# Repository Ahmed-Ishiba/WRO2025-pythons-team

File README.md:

<p align="center">

</p>  

Documentation of our self-driving car for the **WRO 2025 Future Engineers** category.

Our team members:
- **Ahmed Ibrahim Elsayed** — Software lead  
- **Eyad Ahmed Nazary** — Electrical lead  
- **Nour Eldin Raoof** — Mechanical design & fabrication  
- **Omar Khaled** — Coach and mentor  

---

## Content

1. [Project Overview](#project-overview)  
    1. [What is WRO?](#what-is-wro)  
    2. [Team Introduction](#team-introduction)  
    3. [Our Mission](#our-mission)  
2. [System Design](#system-design)  
    1. [Robot Architecture](#robot-architecture)  
    2. [Design Philosophy](#design-philosophy)  
    3. [System Diagram](#system-diagram)  
    4. [Bill of Materials](#bill-of-materials)  
3. [Hardware](#hardware)  
    1. [Mechanical](#mechanical)  
    2. [Electrical](#electrical)  
4. [Software](#software)  
    1. [Brief Overview](#brief-overview)  
    2. [Code flow chart](#flow-chart)  
5. [MATLAB Modeling & Simulation](#modelling-and-simulation)  
    1. [Model Overview](#model-overview)  
    2. [Problem Context and Strategy](#problem-context-and-strategy)  
    3. [Modeling and Simulation](#modelling-and-simulation)
        1. [Simulink Logical Model](#simulink-logical-model)
        2. [Complementary Filter Subsystem](#complementary-filter-sub-system)
        3. [Stateflow Diagram](#state-flow-diagram)
        4. [MATLAB Function](#matlab-function)
        5. [Simscape Electrical Model](#simscape-electrical-model)  
    4. [Testing and Verification](#testing-and-verification)  
6. [Testing & Calibration](#testing-and-calibration)
7. [Reproduce Our Robot: Step-by-Step Guide](#reproduce-our-robot)
8. [Future Improvements](#future-improvements)
9. [Team photo](#team-photo)  

## Project Overview

### What is WRO?

WRO (World Robot Olympiad), specifically the **Future Engineers** category, is a competition created to foster passion for STEM. The Future Engineers category is designed for university students. The challenge changes every 3 years, and this year the theme is **autonomous driving**.  
The robot must be designed to drive around a track **completely autonomously**, without external human intervention.

### Team Introduction

We are the **third generation** of *The Pythons* team.  
Our team consists of 3 members and a coach:

1. **Ahmed Ibrahim Elsayed (me):** Software lead — 2nd year, Faculty of Engineering, Alexandria University  
2. **Eyad Ahmed Nazary:** Electrical lead — 1st year, AASTMT  
3. **Nour Eldin Raoof:** Mechanical lead — 3rd year, Faculty of Science, Alexandria University  
4. **Omar Khaled:** Team coach — AASTMT

We have been participating in robotics competitions since **2016**, and we joined The Pythons team in **2017**.

### Our Mission

Our main mission in robotics competitions is to **improve ourselves**, gain experience, and meet like-minded people.  
We specifically enjoy WRO because it **encourages open-source work**, allowing teams to learn from each other, share solutions, and build stronger communities.
.
## System Design:
  ### Robot architecture:   
The main input sources are the camera, ultrasonic sensors to measure distance from walls, Time Of Flight sensors to measure distance from obstacles and parking lot walls, MPU6050 sensor to measure orientation angle for corner rotation and to ensure parallel parking.  
Then the raspberry pi processes these input data and outputs character to KB2040 to control servo and DC motors

  ### Design philosophy:
  When designing our robot we always made sure that our design follows a modular design that is easy to comprehend and troubleshoot, which helps us in improving it with ease, this approach also minimizes time delays that may happen due to fabrication and unfortunate mishaps, this also helps anyone without experience in robotics and future teams to pick up where we left off.
  ### System diagram:  

This diagram shows the main components of the robot and how they communicate.  
- The Raspberry Pi 5 acts as the central controller, running the main software and decision-making algorithms.  
- It communicates with ESP32 microcontroller and KB2040 via UART.  
- The KB2040 handles all real-time tasks such as controlling the servo and DC motors through PWM signals.  
-  All controllers share a common power source with independent voltage regulation for stability.

<br>  

  ### Bill Of Materials:   
  
| Component Name | Number of Items | Price (EGP) | Price (USD) |
|----------------|-----------------|--------------|--------------|
| Google Coral Accelerator | x1 | 6,250.00 | 125.00 |
| ESP32 Supermini | x1 | 350.00 | 7.00 |
| KB2040 | x1 | 425.00 | 8.50 |
| Raspberry Pi 5 | x1 | 4,000.00 | 80.00 |
| IMU MPU6050 | x1 | 125.00 | 2.50 |
| Step Down Converter 12V→5V | x1 | 450.00 | 9.00 |
| Wheels | x4 | 473.00 | 9.45 |
| Motor | x1 | 350.00 | 7.00 |
| Servo (180°) | x1 | 150.00 | 3.00 |
| Arducam | x1 | 3,000.00 | 60.00 |
| Step Down Converter 12V→3.3V | x2 | 35.00 | 0.70 |
| 12V Battery | x1 | 450.00 | 9.00 |
| Ultrasonic Sensor | x2 | 45.00 | 0.90 |
| Motor Driver IC | x1 | 100.00 | 2.00 |
| Big Ball Bearings | x2 | 100.00 | 2.00 |
| Small Ball Bearings | x2 | 50.00 | 1.00 |
| PCB Fabrication | x1 | 1,250.00 | 25.00 |
|Time Of Flight sensor | x2 | _ | _ |
| **Total** | — | **17,186.50** | **363.41** |
## Hardware:
This section includes brief overview of hardware section of robot (Mechanical and electrical).  
Each section is explained in detail in it's respective folder  
SLDPRT, DXF and board files are also included in their respective folder to download, print and get down to business.  
  ### Mechanical:
  [Mechanical directory](/Mechanical/)     

During the design phase, we chose to stick with a simple structure to save time on fabrication, especially after making a bold decision that I’ll discuss in the next section. Our main focus however was to maximize the steering angles achievable from the servo by creating a fully free movement system, which is vital in turning since we can turn faster and closer to the blocks than other cars. In order to follow the competition's guidelines of using only _**one**_ motor to provide the forward movement to the whole robot we created a gear system to transfer the motor's movement to the rear wheels, also creating a versatile semi movable component mounting system -as seen in the camera mounting- to eliminate the need for refabrication which in turn cuts down the time needed for assembling the robot. 

We also chose big wheels to maximize distance crossed during same revolution this also helps in faster steering.  

  ### Electrical:  
  [Electrical directory](/Electrical/)

You might’ve noticed that our PCB has a rather unusual shape — that’s because it is the shape of our mechanical design!  
This brings us to the bold decision I mentioned earlier: we chose to make the base itself the main circuit.  
This approach not only improves stability and reduces overall size by eliminating separate circuit boards, but also makes assembly incredibly straightforward — every component has its exact place.  

But wait — there’s another bold decision! Did you notice there’s no motor driver on our robot?  
That’s right — we built our own motor driver using a dedicated IC and a decoupling capacitor.  
This approach helped us further reduce the robot’s size by eliminating the need for bulky modules like the L298N or Cytron drivers.

## Software:
In this section I will also only provide overview on code and thought process since line-by-line documentation can be found in the [Software directory](/Software/).  

  ### Brief overview:
  For our software and programming I divided it into 3 sections: 
  - Wall tracking
  -  Obstacle Avoidance
  -  Corner detection
  -  Parking
1. Wall Tracking:
   For wall tracking I calculated wall area difference that camera sees and wall difference measured from ultrasonic sensors then used sensor fusion to get accurate data that    I then passed to a PID controller to center the robot all processed on the raspberry pi 5.
   
2. Obstacle Avoidance:
    For obstacle avoidance we used a custom trained yolov8 AI model with 500+ pictures to make sure that the robot detects the traffic signs regardless of environment.
    This approach is better than the traditional image processing approach that relies on the environment since HSV values change according to reflected light.
    Our AI model runs on the google edge TPU to achieve high FPS and faster detection.

  https://github.com/user-attachments/assets/0746ed6e-e767-420a-9b96-121c0c189ac0

3. Corner detection:
   For corner detection we used simple image processing algorithms that detect blue and orange strips using the HSV values of each color to apply masks
   
4. Parking:
   IN PROGRESS  
  ### Flow Chart:   

## Modelling and simulation:
  ### Model Overview:  
  Here we will not go into much detail, you can find a detailed explanation, model files and statflow files in the [Modelling and simulation directory](/Modeling%20and%20simulation/)  
  </br>
  When designing our wall centering algorithm we used the simplest algorithm possible due to how hard it is to tune advanced control algorithms like PID or applying filters, however when MathWorks created this award we had no reason not to use it and apply any algorithm we wanted especially after giving us license for the newest MATLAB version for free.  
  </br>
  now we can apply all the algorithms we want and all my crazy ideas, here is what we did:  
  When centering in the previous algorithm we only used the area of the 2 walls seen by our arducam however it was really noisy and changes too fast which is not that good for wall centering, however when we tried to use an ultrasonic sensor the distance readings where precise but the rate at which it changes was really slow  
  </br>
  so now we have 2 methods to measure the same thing each have their pros and cons so we got the idea to fuse them both with a simple weighted sum formula so we can have control over it and ensure it's smoothness  
  
  After we get the result of the formula which measures the deviation of the robot from the center of the lane we then pass it into a PID controller then we take the output of the controller and pass it into a map function that we implemented myself in order to convert the range of the PID output into a range that my servo accepts(from 0 to 180)  
  
  ### Problem context and strategy:  
  the main challenges that we faced were:  
  - Creating the weighted sum formula and tuning the weights
  - Tuning the PID
  - Making sure the map function works correctly
  - and a problem that we realised later is that I don't know how to test this!
  - simulating our electrical system on simscape electrical  

  As for our strategy:   
  1. we started by writing pseudo code for my algorithm and knew it's building blocks
  2. For simplicity we divided this algorithm into 5 parts: the complementary filter, the PID controller, the map function, creating a stateflow diagram and simulating the circuit we then tackled each in this order
  3. we then decided what MathWorks products help with this which were: Simulink for creating a subsystem for my filter and use it's wide variety of blocks to save time on implementing a PID algorithm from scratch, MATLAB for writing code of our mapping function, simscape electrical for simulating my electrical system and stateflow for creating a diagram of my algorithm using states  
  </br>   
  Using MATLAB, Simulink, simscape and state flow saved so much time and were extremely helpful   

  - using MATLAB for writing the mapping code was extremely easy especially with MATLAB's easy syntax
  - Simulink was by far the best tool we used because not only can we tune algorithms and filters without needing any hardware we can just tune it with only clicking one button! not to mention the clear modular look that helped me troubleshoot where exactly our model went wrong, the graphing that helps us understand the behaviour of our robot and derive meaningful data from it and realizing logical problems in minutes that would've taken days to realize
  - stateflow was really helpful in dividing the algorithm like a flow chart but much briefly, helped us in verifying my code since the code is divided into states just like stateflow and it also helped us in verifying condition if changing states and overall is a vital tool
  - simscape electric was used for simulating our circuit and finding out stall current, max current draw and we used it to correct our choice of battery since we kept having power issues but using simscape we corrected a mistake that would've cost us the competition, this is also a tool that we would definitely use for future robotics projects

  ### Modelling and simulation:  
  #### Simulink logical model:  
  
  now for the main model as I said everything is explained in detail in the [Modelling directory.](/Modeling%20and%20simulation/)  

  This is the main model and as you can see we take input from 2 sources that somewhat measure the same thing then pass it into our complementary filter that outputs an estimated deviation from the center of the lane and passes it to a PID controller and finally map it to servo range using the map function and send it to the servo  
  
 this algorithm is from my perspective as simple as it gets while at the same time maintaining it's simplicity for fast and easy troubleshooting (not that there is room for error after tuning it)  

#### Complementary filter sub-system:  

 For the complementary filter we created a sub-system for it which is by far the most useful feature in simulink since the logic for the filter is very confusing when put with the main system, here is the diagram for the complementary filter (explained in detail in the modelling directory):  

#### State-flow diagram:   

  Here is the stateflow diagram for you to understand how our code is divided  

#### MATLAB function:   

Here is the mapping function we implemented which is just a mathematical formula nothing too complicated   

#### Simscape electrical model:   
We used simscape electrical to measure our maximum ampere consumption, required voltage and suitable battery capacity, here is a photo of our model:   

  ### Testing and verification:   
  #### Testing Logical model:   
  
  For testing this model we had to think and come up with ideas we then came to the conclusion to use the simulink function generator  
  
  we used a sin wave to simulate changing input and we of course got an output in shape of sin wave which is both scientifically and physically correct since this model is considered a linear time-invariant system so only the amplitude changes and physically correct since when error increases from the setpoint(the rise of the sine wave) the output should also increase to compensate and correct this error  

this is the graph of the complementary filter and the PID controller and above it is the model but we used the sin generator as the input.

This is the output(servo degree) resulting from the model and as you can see it changes reasonably with the changing the input both following the same graph  

</br>
We also used step function generator to simulate specific cases that I encountered when working on my robot and coincidentally found them

this is the output (servo degree) resulting from our model and above it is the model using the step function generator  

</br>

#### Testing the electrical model:  

As for testing our electrical model it was as easy as hitting run then seeing the output voltage and current intensity on our scope  

 As you can see we got a max current draw of 7 Amps and voltage of approximately 11.1 volts so we made our decision for battery type by dividing available battery capacities on the internet by the max current and getting how long it will last.  

## Testing and calibration:
After completing the robot assembly, we performed a series of tests to ensure that every subsystem was functioning correctly.
We ran the test scripts located in the [Software Testing Directory](/Software/System%20Testing/)

- Communication between the microcontrollers and sensors
- Sensor testing and calibration
- Motor operation and direction control
- Servo steering response
- Camera functionality and data transmission

## Reproduce Our Robot:  
A [Raspberry pi setup script](/raspberrypi_setup.sh) is included that setups all required packages 
1. First start with the main body of robot (after buying components of course)
2. Fabricate the pcb since this is the body or if you want to wire everything and don't need a pcb just download our solidworks files and cnc cut it
3. assemble the robot by connecting everything to the pcb like labeled in our fusion360 file or connect using jumper wires
4. setup the raspberry pi and enable i2c and uart
5. clone this repo on raspberry pi
6. test the system using the files in the [Software testing directory](/Software/System%20Testing/)
7. After making sure every component in the system is running normally, run the main code
8. Now you have a working WRO Future engineers self-driving car!

## Future improvements:
In the future if we participate again and for other teams looking at this repo here are some improvements I wished to implement:
- Use better sensor fusion algorithms
- Create a Simulink environment specifically for this competition like the one in robotics playground
- Better weight distribution in the robot design
- Put built-in voltage sensor
- add cloud-based data logging for better debugging
- create a GUI that combine camera frame and terminal output (looks cool no other reason)
## Team photo:

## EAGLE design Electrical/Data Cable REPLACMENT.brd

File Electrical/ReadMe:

Electrical schematics and boards

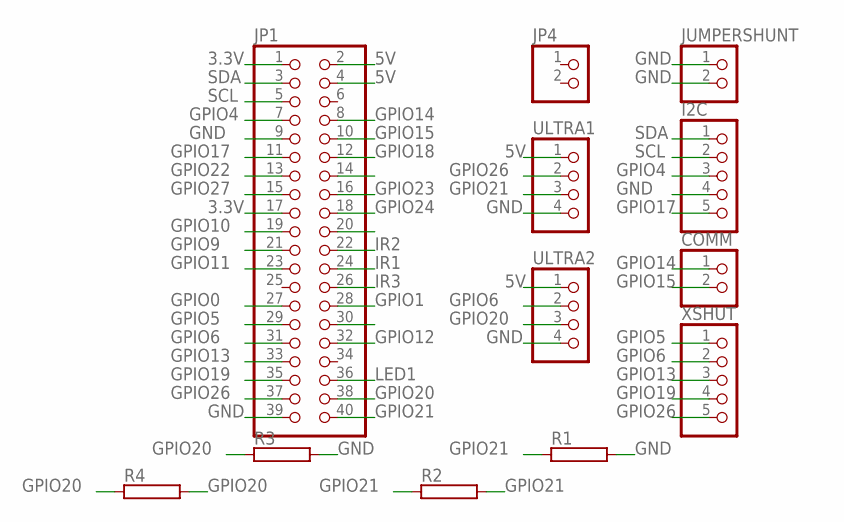
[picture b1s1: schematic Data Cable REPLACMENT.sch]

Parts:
COMM: PINHD-1X2; 1X02
I2C: PINHD-1X5; 1X05
JP1: PINHD-2X20; 2X20
JP4: PINHD-1X2; 1X02
JUMPERSHUNT: PINHD-1X2; 1X02
R1, R2, R3, R4: RHPS58; HPS58
ULTRA1, ULTRA2: PINHD-1X4; 1X04
XSHUT: PINHD-1X5; 1X05

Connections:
3.3V: JP1.1, JP1.17
5V: JP1.2, JP1.4, ULTRA1.1, ULTRA2.1
GND: I2C.4, JP1.9, JP1.39, JUMPERSHUNT.1, JUMPERSHUNT.2, R1.2, R3.2, ULTRA1.4, ULTRA2.4
GPIO0: JP1.27
GPIO1: JP1.28
GPIO4: I2C.3, JP1.7
GPIO5: JP1.29, XSHUT.1
GPIO6: JP1.31, ULTRA2.2, XSHUT.2
GPIO9: JP1.21
GPIO10: JP1.19
GPIO11: JP1.23
GPIO12: JP1.32
GPIO13: JP1.33, XSHUT.3
GPIO14: COMM.1, JP1.8
GPIO15: COMM.2, JP1.10
GPIO17: I2C.5, JP1.11
GPIO18: JP1.12
GPIO19: JP1.35, XSHUT.4
GPIO20: JP1.38, R3.1, R4.1, R4.2, ULTRA2.3
GPIO21: JP1.40, R1.1, R2.1, R2.2, ULTRA1.3
GPIO22: JP1.13
GPIO23: JP1.16
GPIO24: JP1.18
GPIO26: JP1.37, ULTRA1.2, XSHUT.5
GPIO27: JP1.15
IR1: JP1.24
IR2: JP1.22
IR3: JP1.26
LED1: JP1.36
SCL: I2C.2, JP1.5
SDA: I2C.1, JP1.3

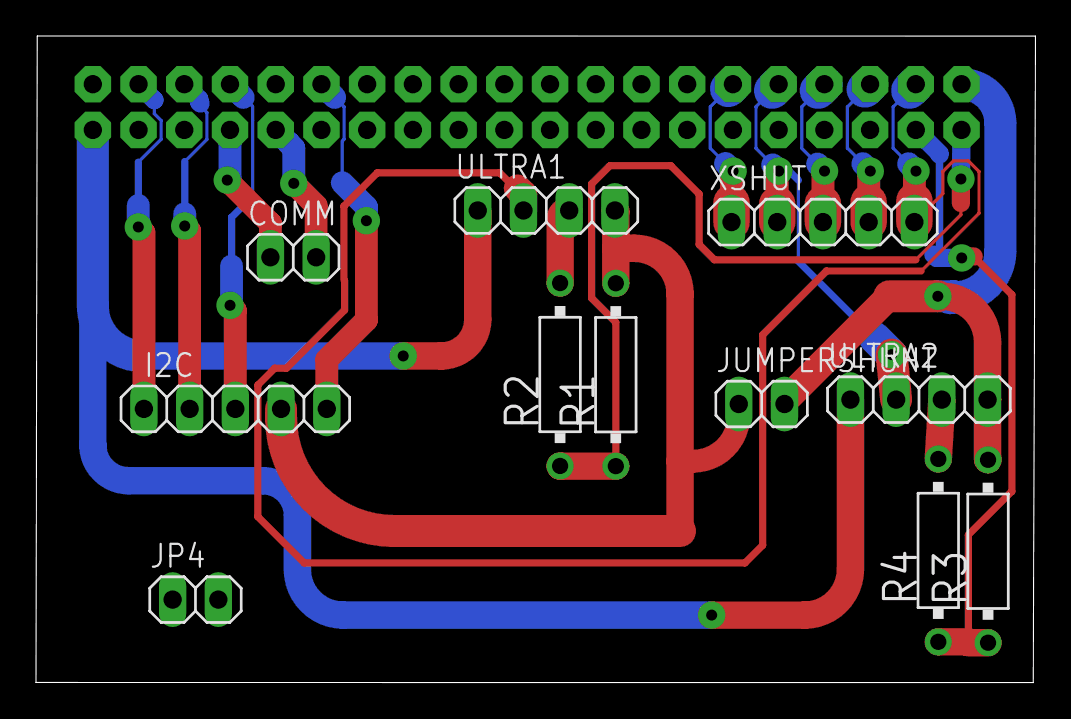
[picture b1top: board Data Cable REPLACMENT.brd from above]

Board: 2 copper layers, 55.5 x 35.9 mm, 12 parts (1 on the bottom side), 16 nets.

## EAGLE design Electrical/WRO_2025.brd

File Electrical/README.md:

# Electrical schematics and boards:

The following are schematic files that showcase the circuit of our robot and the board files are used to fabricate the PCB

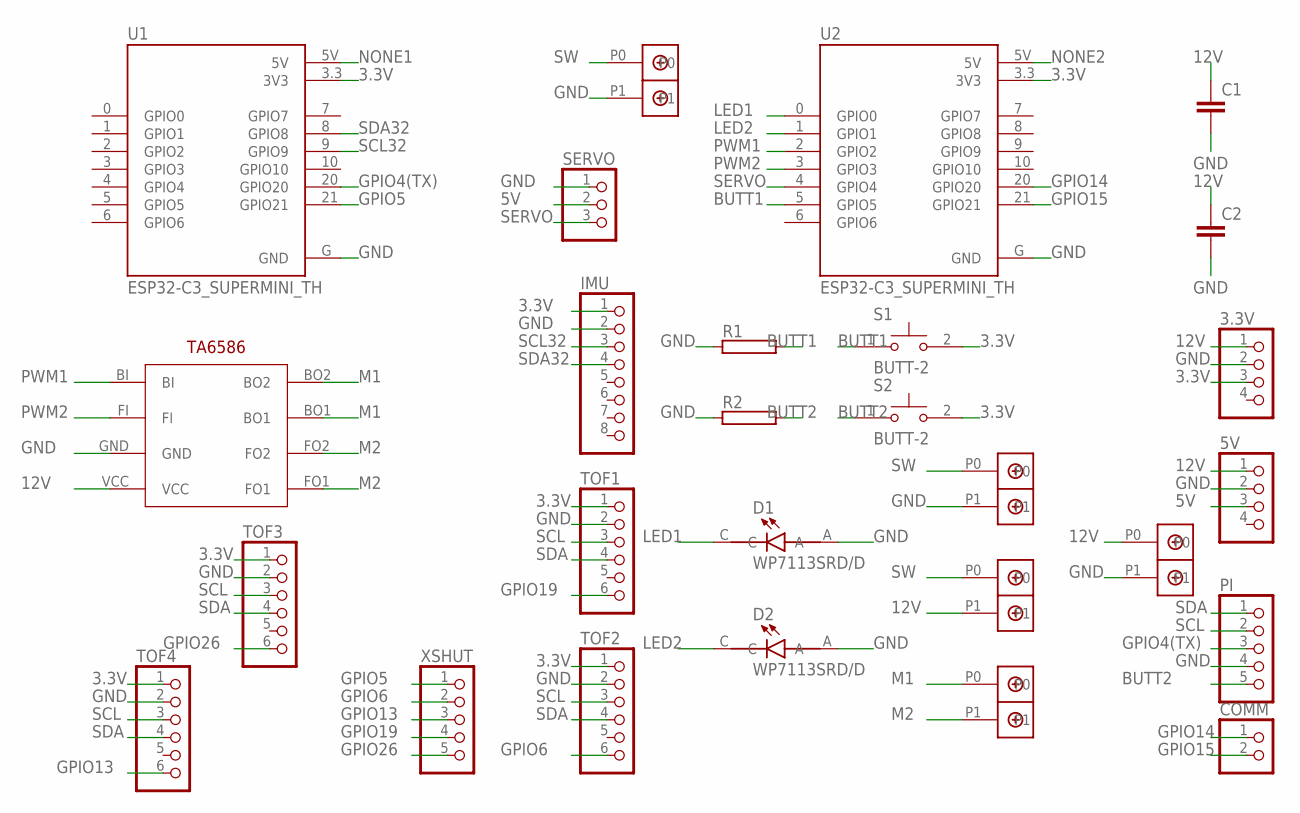
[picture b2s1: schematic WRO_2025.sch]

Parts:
3.3V, 5V: PINHD-1X4; 1X04
C1, C2: C2,5-3; C2.5-3
COMM: PINHD-1X2; 1X02
D1, D2: WP7113SRD/D; LED_WP7113SRD/D
IMU: PINHD-1X8; 1X08
PI: PINHD-1X5; 1X05
R1, R2: RHPS58; HPS58
S1, S2: BUTT-2; SW_BUTT-2
SERVO: PINHD-1X3; 1X03
TOF1, TOF2, TOF3, TOF4: PINHD-1X6; 1X06
U1, U2: ESP32-C3_SUPERMINI_TH; MODULE_ESP32-C3_SUPERMINI_TH
U$1, U$2, U$3, U$5, U$6: DBCONN-1X2
U$4: TA6586; TA6586-FOOTPRINT
XSHUT: PINHD-1X5; 1X05

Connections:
3.3V: 3.3V.3, IMU.1, S1.2, S2.2, TOF1.1, TOF2.1, TOF3.1, TOF4.1, U1.3.3 (3V3), U2.3.3 (3V3)
5V: 5V.3, SERVO.2
12V: 3.3V.1, 5V.1, C1.1, C2.1, U$2.P1, U$4.VCC, U$5.P0
BUTT1: R1.2, S1.1, U2.5 (GPIO5)
BUTT2: PI.5, R2.2, S2.1
GND: 3.3V.2, 5V.2, C1.2, C2.2, D1.A, D2.A, IMU.2, PI.4, R1.1, R2.1, SERVO.1, TOF1.2, TOF2.2, TOF3.2, TOF4.2, U1.G (GND), U2.G (GND), U$1.P1, U$4.GND, U$5.P1, U$6.P1
GPIO4(TX): PI.3, U1.20 (GPIO20)
GPIO5: U1.21 (GPIO21), XSHUT.1
GPIO6: TOF2.6, XSHUT.2
GPIO13: TOF4.6, XSHUT.3
GPIO14: COMM.1, U2.20 (GPIO20)
GPIO15: COMM.2, U2.21 (GPIO21)
GPIO19: TOF1.6, XSHUT.4
GPIO26: TOF3.6, XSHUT.5
LED1: D1.C, U2.0 (GPIO0)
LED2: D2.C, U2.1 (GPIO1)
M1: U$3.P0, U$4.BO1, U$4.BO2
M2: U$3.P1, U$4.FO1, U$4.FO2
NONE1: U1.5V
NONE2: U2.5V
PWM1: U2.2 (GPIO2), U$4.BI
PWM2: U2.3 (GPIO3), U$4.FI
SCL: PI.2, TOF1.3, TOF2.3, TOF3.3, TOF4.3
SCL32: IMU.3, U1.9 (GPIO9)
SDA: PI.1, TOF1.4, TOF2.4, TOF3.4, TOF4.4
SDA32: IMU.4, U1.8 (GPIO8)
SERVO: SERVO.3, U2.4 (GPIO4)
SW: U$1.P0, U$2.P0, U$6.P0

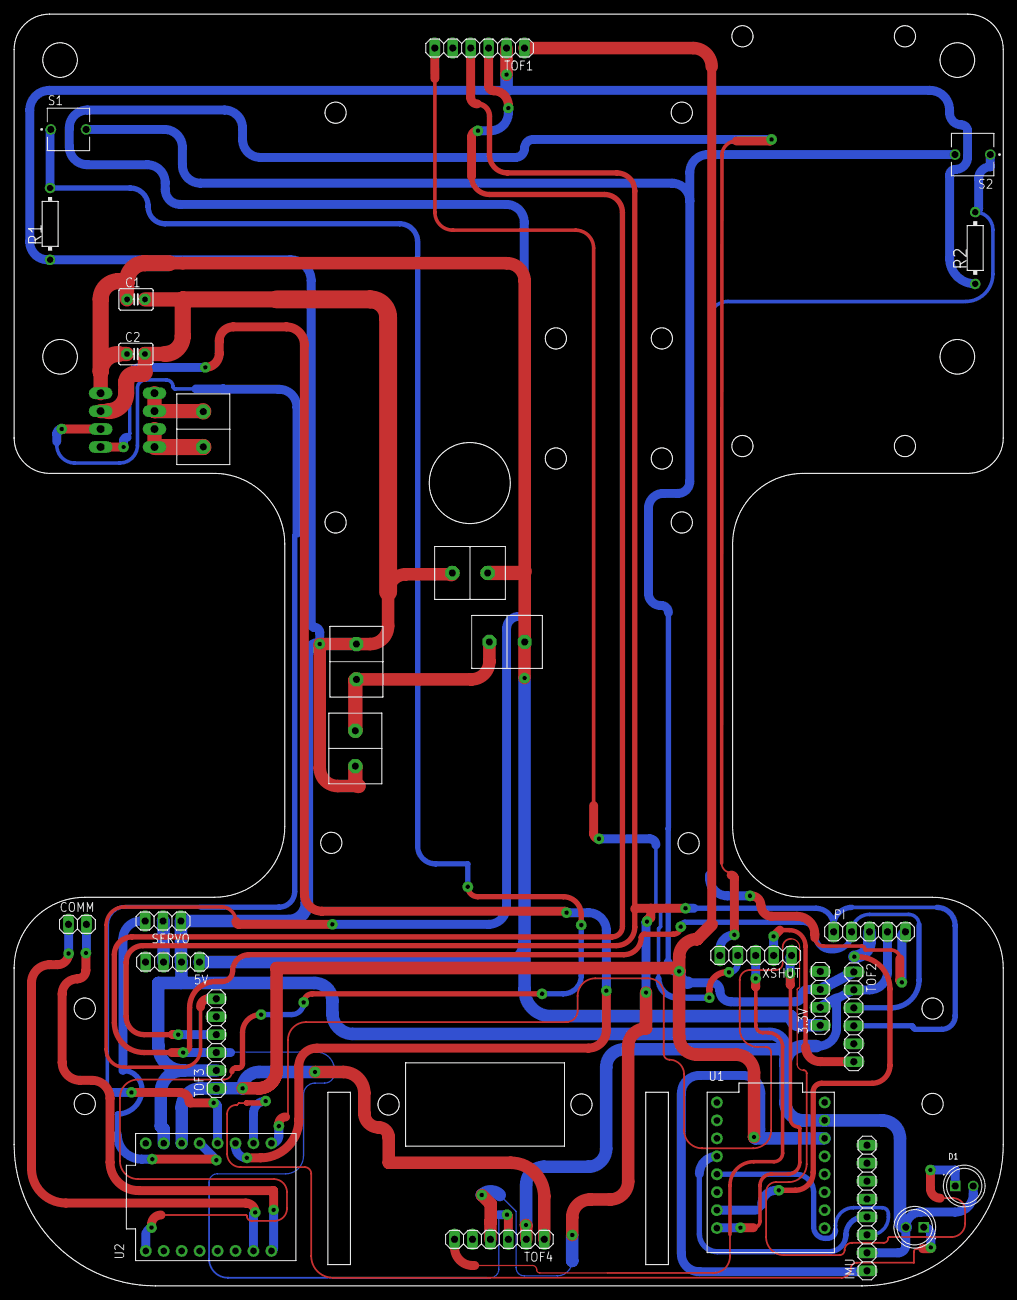
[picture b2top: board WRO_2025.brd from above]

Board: 2 copper layers, 140.0 x 180.0 mm, 27 parts (1 on the bottom side), 26 nets.

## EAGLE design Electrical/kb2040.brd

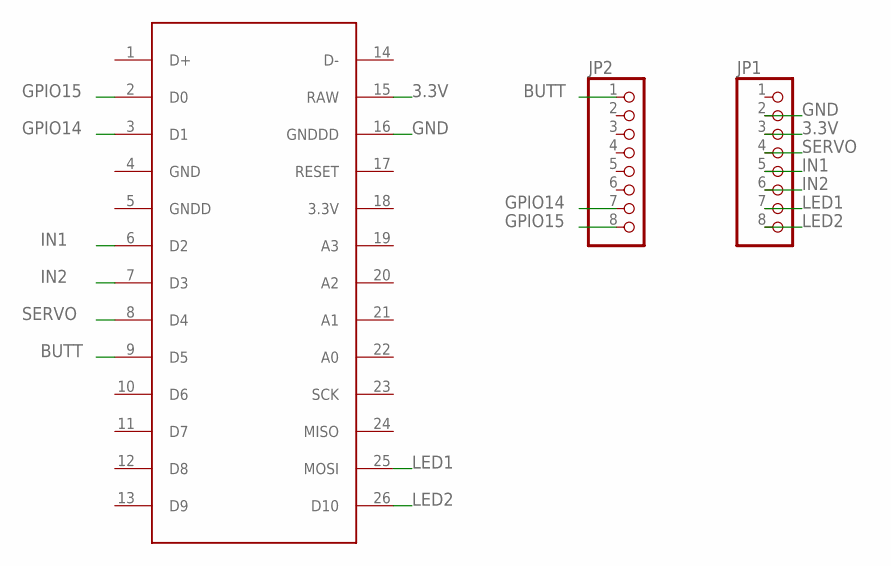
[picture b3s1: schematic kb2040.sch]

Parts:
JP1, JP2: PINHD-1X8; 1X08
U$1: KB2040

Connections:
3.3V: JP1.3, U$1.15 (RAW)
BUTT: JP2.1, U$1.9 (D5)
GND: JP1.2, U$1.16 (GNDDD)
GPIO14: JP2.7, U$1.3 (D1)
GPIO15: JP2.8, U$1.2 (D0)
IN1: JP1.5, U$1.6 (D2)
IN2: JP1.6, U$1.7 (D3)
LED1: JP1.7, U$1.25 (MOSI)
LED2: JP1.8, U$1.26 (D10)
SERVO: JP1.4, U$1.8 (D4)

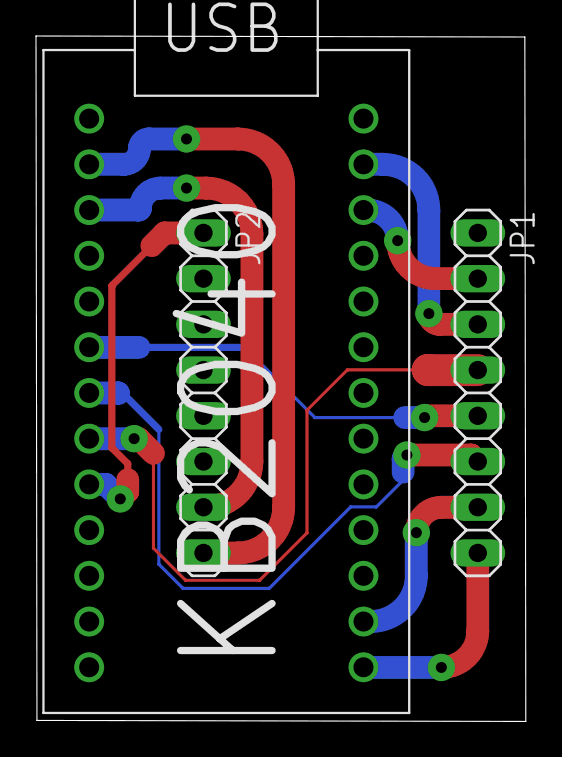
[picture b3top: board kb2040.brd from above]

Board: 2 copper layers, 27.2 x 38.1 mm, 3 parts (0 on the bottom side), 10 nets.

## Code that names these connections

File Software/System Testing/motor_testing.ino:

#include <Servo.h>

Servo myservo;  // create Servo object to control a servo
// twelve Servo objects can be created on most boards

#define SERVO_PIN 4
#define MOTOR_PIN_A 2
#define MOTOR_PIN_B 3  
#define BUTTON1_PIN 5
#define BUTTON2_PIN 6
#define LED1_PIN 10
#define LED2_PIN 11

int pos = 0;    // variable to store the servo position
int i =1;
void setup() {
  myservo.attach(4);  // attaches the servo on pin 9 to the Servo object
    pinMode(MOTOR_PIN_A, OUTPUT);
  pinMode(MOTOR_PIN_B, OUTPUT);
}

void loop() {
      myservo.write(100);
      if(i ==1){
      i++;
      analogWrite(MOTOR_PIN_A, 0);
      analogWrite(MOTOR_PIN_B, 200);
      delay(2000);
      
      }
      else{
      analogWrite(MOTOR_PIN_A, 0);
      analogWrite(MOTOR_PIN_B, 0);
      }
}

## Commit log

2025-09-16 Add initial ReadMe for Mechanical files
2025-09-16 Add initial content to ReadMe for Electrical section
2025-09-16 Enhance README with team and software system information
    Expanded documentation to include team members and software system details.
2025-09-16 Update README to remove software system section
    Removed software system details from README.
2025-09-16 Added design files for the robot.
2025-09-16 Add README with software system overview
    Added initial content to the README file explaining the software system and robot centering algorithms.
2025-09-16 Rename ReadMe to README.md
2025-09-16 Add qualification_code.py for navigation and detection
    This script utilizes a camera and ultrasonic sensors to navigate and detect colored corners, controlling a device based on sensor input.
2025-09-16 Added .brd and .sch files for the robot
2025-09-16 Add README for system testing procedures
2025-09-16 Add camera test script using Picamera2 and OpenCV
2025-09-16 Add Serial_communication.py for yaw control
    Implement serial communication for yaw angle control.
2025-09-16 Add ultrasonic sensor test script
2025-09-16 Add motor control and servo setup
    Implement motor control and servo positioning in motor_testing.ino
2025-09-16 Add MPU6050 sensor test code
    This code initializes and configures the MPU6050 sensor, enabling its Digital Motion Processor (DMP) and reading yaw, pitch, and roll values in a loop.
2025-09-27 added main code files
2025-09-27 Add team photo to project documentation
    Added a team photo to the README.
2025-09-27 Enhance README with details on schematics and boards
    Added a brief description of schematic and board files.
2025-09-27 Update README with box detection and code flow details
    Expanded README to include box detection and general flow of code.
2025-09-27 Add robot photo section to README
    Added a section for the robot photo to the README.
2025-10-27 Enhance README with project overview and structure
    Expanded documentation with structured content sections and team details.
2025-10-28 Added Untitled Diagram.drawio.svg
2025-10-28 Added computer_architecture.drawio.svg
2025-10-28 Added Untitled Diagram.drawio
2025-10-28 Enhance README with robot design details
    Added detailed sections on robot architecture, design philosophy, system diagram, and bill of materials.
2025-10-28 Refactor README for clarity and formatting
    Removed unnecessary line breaks and improved formatting in the README file. Added brief overview of hardware section and clarified design decisions regarding mechanical and electrical components.
2025-10-28 Revise README with new system diagram and software details
    Updated system diagram and added software overview.
2025-10-28 Revise design philosophy and update system diagram
    Updated system diagram image and improved design philosophy description.
2025-10-28 Update README with testing and future improvements
    Added testing and calibration details to README.
2025-10-29 Update README with project and team information
    Added team member details and project overview to README.
2025-11-05 Enhance README with detailed modeling and simulation info
    Expanded the Modeling & simulation section with detailed explanations of the algorithm, methods, and tools used for the project. Added subsections for Project Overview and Problem context and strateg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
2025-11-05 Change 'Project Overview' to 'Model Overview'
    Updated section titles in the README for consistency.
2025-11-05 Update section title for modeling & simulation
2025-11-05 Fix typo in README.md link to simulation directory
2025-11-05 Update README.md
    Changed robot picture to a more updated one.
2025-11-05 Update README.md
    Expanded the Mechanical Section's Description
2025-11-05 Update README.md
    Expanded upon the Mechanical Section's Description.
2025-11-05 Update README.md
    Lightly Modified the Mechanical Section's Description
2025-11-06 Refactor README structure and formatting
    Updated the README.md to improve the structure of the content and fix formatting issues.
2025-11-06 Revise README for clarity and structure
    Updated README.md to enhance clarity and structure. Improved team member roles, project overview, and system design sections.
2025-11-06 Fix typos and update section headings in README
    Correct typos and improve formatting in README.
2025-11-06 Update README with reproduction guide and TOC changes
    Added a step-by-step guide for reproducing the robot and updated the table of contents.
2025-11-06 Add team photo section to README
    Added a team photo section to the README.
2025-11-06 Revise README with Raspberry Pi details and algorithms
    Updated README to reflect changes in the Raspberry Pi system and added detailed explanations for the complementary filter and PID controller implementations.
2025-11-06 Update Block Diagram section to Flow Chart
2025-11-07 Revise competition history and hardware details
    Updated team participation years and hardware specifications.
2025-11-07 Clean up README by removing duplicates
    Removed duplicate link and adjusted section numbering.
2025-11-07 Correct capitalization in design philosophy section
2025-11-07 Fix voltage intensity graph image source
    Updated image source for voltage intensity graph in README.
2025-11-07 Fix image tag for voltage intensity graph
2025-11-07 Enhance README with model explanations and instructions
    Added detailed explanations for electric model, map function, and Simulink model. Included step-by-step instructions and system component descriptions.
2025-11-07 Add Raspberry Pi setup script for AI environment
    This script sets up a Raspberry Pi environment with I2C, Python, NumPy, OpenCV, and Coral TPU Runtime.
2025-11-07 Add Raspberry Pi setup script instructions to README
    Added a note about the Raspberry Pi setup script for easier reproduction of the robot.
2025-11-07 Enhance README with directory links and new section
    Updated README to include links to Mechanical and Electrical directories, added corner detection section, and improved clarity in software overview.
2025-11-07 Revise README for mechanical design details
    Updated the README to provide detailed descriptions of the mechanical design, including the drive and steering systems, along with images.
2025-11-07 added all updated files
2025-11-08 Add contributor badge for Nour Eldin Raoof
